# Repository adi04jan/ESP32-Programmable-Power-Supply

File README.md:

# Voltbench — ESP32-C3 Programmable Power Supply

A three-channel bench power supply controlled over Wi-Fi, built around an **ESP32-C3 Super Mini**. The variable channel uses an LM2596-ADJ buck converter set by an MCP4017 I2C digital potentiometer, driven by a calibration-map "deadbeat" controller: it jumps to the mapped wiper step, verifies with one filtered ADC sample, applies at most one single-step correction, and freezes — no hunting, settled in under a second. Two fixed rails deliver regulated 5 V and 3.3 V. Everything is managed through a dark-themed responsive web UI served directly from the microcontroller — no app, no cloud, no dependencies.

Designed and developed by **Aditya Biswas**.

---

## Screenshots

| Dashboard | History | Settings |
|-----------|---------|----------|
|  |  |  |

---

## Features

### Power Outputs
| Channel | Rail | Range | Regulation |
|---------|------|-------|------------|
| CH1 | LM2596-ADJ (variable) | 2.5 V – 15 V | map-based deadbeat control + on-device calibration sweep |
| CH2 | Mini360 (fixed 5 V) | 5.0 V | Passthrough (monitor only) |
| CH3 | LM1117-3.3 (LDO, fixed) | 3.3 V | Passthrough (monitor only) |

### Accuracy (measured, after calibration sweep)
| Setpoint | Measured | Error |
|----------|----------|-------|
| 3.3 V | 3.22 V | −80 mV (2.4%) |
| 5.0 V | 4.99 V | −10 mV (0.2%) |
| 9.0 V | 8.98 V | −20 mV (0.2%) |
| 12.0 V | 12.29 V | +290 mV (2.4%) |
| 15.0 V | 15.55 V | +550 mV (3.7%) |

> Accuracy is limited by wiper-step quantization (~27 mV/step at low voltages, up to ~1 V/step near the ceiling). Run Settings → Calibration → Run sweep once after assembly (CH1 unloaded).

### Web UI
- **Dashboard** — live voltage at 4 Hz, per-channel enable toggles, voltage slider, preset chips (right-click to delete, ＋ to save current), delta indicator, All Off button
- **History** — bezier-smoothed time-series graph with SMA noise reduction, channel filters, event markers (output on/off), adjustable time window (1 min – 12 h)
- **Settings** — mDNS hostname, security/login, Wi-Fi management (scan/connect/forget, stores up to 4 SSIDs), OTA update, experimental flags (dial mode, EMA smoothing, fast poll), MQTT bridge
- **Calibration card** — run/clear the CH1 calibration sweep and see whether a valid map is loaded
- **Device log pane** — live firmware log streamed over a view-only WebSocket (`/logws`)
- **Web-upload OTA** — flash a `.bin` straight from the browser, with real upload/flash progress

### Connectivity
- **WebSocket** `/ws` — server pushes full status JSON at up to 4 Hz; also accepts control commands
- **REST API** — full control and configuration via `/api/*` endpoints
- **mDNS** — reachable at `http://voltbench.local/` on any mDNS-capable host (Windows, macOS, Linux, iOS)
- **Captive portal** — automatically falls back to AP mode (`VoltbenchAP`) when no saved Wi-Fi connects; re-tries every 30 s
- **Telnet console** (`:23`) and USB serial console — single-letter commands: `v<volts>` set CH1, `o1`/`o0` output on/off, `m` run calibration sweep, `c` cal status, `?` full state dump

### Management
- **OTA update** — pulls firmware from this repo's GitHub "latest release" assets on demand or auto-check on boot; web-upload OTA as a second, USB-free path
- **NVS persistence** — all settings, the CH1 calibration map, and Wi-Fi credentials survive power cycles and OTA updates
- **MQTT bridge** — publishes 1 Hz telemetry; subscribes to control topics
- **Factory reset** — wipes all NVS from Settings → Factory Reset
- **Token auth** — optional bearer-token login (stored in `sessionStorage`, persists across reboots)

---

## Hardware

### Bill of Materials

| Component | Part | Notes |
|-----------|------|-------|
| MCU | ESP32-C3 Super Mini | 4 MB flash, Wi-Fi 802.11 b/g/n |
| Variable regulator | LM2596-ADJ module | Adjustable buck, ~3–35 V input |
| Fixed 5 V | Mini360 module | Fixed-output synchronous buck |
| Fixed 3.3 V | LM1117-3.3 | LDO, TO-92 or SOT-223 |
| Digital pot | MCP4017T-103E/LT | 10 KΩ, 128 steps, I2C @ 0x2F |
| R1 (feedback) | 10 KΩ 1% | VOUT → FB (ADJ) on LM2596 |
| R_adc_top | 47 KΩ | CH1 ADC voltage divider high-side |
| R_adc_bot | 1 KΩ | CH1 ADC voltage divider low-side |
| R_5v / R_3v3 | 10 KΩ × 4 | CH2 and CH3 ADC dividers (÷2 each) |
| Enable switches | N-ch MOSFET or relay × 3 | Logic-level control from GPIO 5/6/7 |

### Pin Map

| GPIO | Function |
|------|----------|
| 0 | ADC CH1 — variable rail (47K:1K divider, ×48 scale) |
| 1 | ADC CH2 — 5 V rail (10K:10K divider, ×2 scale) |
| 3 | ADC CH3 — 3.3 V rail (10K:10K divider, ×2 scale) |
| 5 | Enable CH1 (variable output) |
| 6 | Enable CH2 (5 V output) |
| 7 | Enable CH3 (3.3 V output) |
| 8 | I2C SDA → MCP4017 |
| 9 | I2C SCL → MCP4017 |

### LM2596-ADJ Feedback Network

```
VOUT ──── 10 KΩ ──── FB (ADJ) ──── MCP4017 wiper ──── GND
                                     (0 – 10 KΩ)
```

`Vout = 1.235 × (1 + 10 000 / R2)` where R2 is the MCP4017 resistance.

| Target | R2 needed | MCP4017 step |
|--------|-----------|--------------|
| 2.5 V | 9.87 KΩ | 125 / 127 |
| 5.0 V | 3.27 KΩ | 41 / 127 |
| 9.0 V | 1.56 KΩ | 20 / 127 |
| 12.0 V | 1.13 KΩ | 14 / 127 |
| 15.0 V | 0.87 KΩ | 11 / 127 |

### CH1 ADC Divider

```
VOUT ──── 47 KΩ ──── GPIO0 ──── 1 KΩ ──── GND
                       ↑
                  ADC reads here (0 – 2.5 V with ADC_11db)
                  Scale factor = 48 → supports up to ~27 V
```

---

## Firmware

### Prerequisites

- **Arduino IDE 2.x** with ESP32 Arduino core (Espressif) v3.x
- Libraries (Library Manager):
  - `ESPAsyncWebServer` + `AsyncTCP`
  - `ArduinoJson` v7
  - `PubSubClient` *(only if MQTT is needed)*

  (The MCP4017 digital pot is driven with direct I2C register writes — no digital-pot library needed.)

### Build & Flash

1. Clone the repository:
   ```sh
   git clone https://github.com/your-username/ESP32-Programmable-Power-Supply.git
   ```

2. Edit `ESP32_power_supply/credential.h` with your Wi-Fi credentials (these only seed NVS the first time — if any SSID slot is already saved, they're ignored):
   ```cpp
   static const char *ssids[]     = { "YourSSID" };
   static const char *passwords[] = { "YourPassword" };
   ```
   OTA is not configurable here — it's pinned to this repo's GitHub "latest release" assets (see [OTA Updates](#ota-updates)).

3. In Arduino IDE, set:
   - Board: `ESP32C3 Dev Module`
   - Upload Speed: `921600`
   - Flash Size: `4MB`
   - Partition Scheme: **Custom** → select `ESP32_power_supply/partitions.csv`

4. Upload: **Sketch → Upload** (`Ctrl+U`)

5. Open Serial Monitor at **115200 baud** — you should see:
   ```
   Voltbench v3.0.0 booting...
   MCP4017 OK @ 0x2F
   Joined YourSSID — IP=192.168.x.x
   URL: http://voltbench.local/
   ```

6. Open `http://voltbench.local/` in any browser on the same network.

### Partition Layout

```
nvs        20 KB   Settings and Wi-Fi credentials
otadata     8 KB   OTA slot tracking
app0     1792 KB   Active firmware (~1.3 MB used)
app1     1792 KB   OTA staging slot
spiffs    448 KB   Reserved
```

### Regenerating the Web UI

After editing `new design/Power Supply.html`, run this PowerShell snippet to rebuild `web_page.h`:

```powershell
$html  = Get-Content "new design\Power Supply.html" -Raw -Encoding utf8
$bytes = [System.Text.UTF8Encoding]::new($false).GetBytes($html)
$ms    = [System.IO.MemoryStream]::new()
$gz    = [System.IO.Compression.GzipStream]::new($ms, [System.IO.Compression.CompressionLevel]::Optimal)
$gz.Write($bytes, 0, $bytes.Length); $gz.Close()
$gzBytes = $ms.ToArray()
$chunks  = for ($i = 0; $i -lt $gzBytes.Length; $i += 16) {
    "  " + (($gzBytes[$i..([Math]::Min($i+15,$gzBytes.Length-1))] |
    ForEach-Object { "0x{0:x2}" -f $_ }) -join ", ")
}
$header = @("#pragma once","const uint8_t index_html_gz[] PROGMEM = {",
            ($chunks -join ",`n"),"};",
            "const size_t index_html_gz_len = $($gzBytes.Length);")
[System.IO.File]::WriteAllLines("ESP32_power_supply\web_page.h", $header,
    [System.Text.UTF8Encoding]::new($false))
Write-Host "Done: $($bytes.Length) -> $($gzBytes.Length) bytes"
```

---

## Usage

### Calibration

On first flash CH1 has no calibration map, so the deadbeat controller falls back to a coarse built-in estimate. For rated accuracy, run the sweep once:

1. **Disconnect any load from CH1** — the sweep drives the output across its full range (~2.5 V → ceiling) and needs the rail unloaded to read clean.
2. In **Settings → Calibration**, click **Run sweep**. It steps the MCP4017 through all 128 positions, sampling each one — takes about a minute. The busy state is reported as `"busy"` in `/api/status` and rejects a second sweep request while running.
3. The resulting step→millivolt map is smoothed to be monotonic, marked valid, and persisted to NVS — it survives reboots and OTA updates (NVS is a separate flash partition the OTA slot swap never touches).

Re-run the sweep only if the hardware changes (different MCP4017, feedback resistor, or LM2596 module). Use **Clear** to wipe the map and fall back to the coarse estimate.

### Presets

- **Click** a preset chip to jump to that voltage instantly.
- **Right-click** a chip to delete it.
- **＋** saves the current slider position as a new preset (stored in browser `localStorage`).

### All Off

The **All off** button in the top-right cuts all three outputs simultaneously. Individual toggles restore each channel independently.

---

## REST API

All responses are JSON. When `require_login` is enabled, include header `X-Auth: <token>` on every request except `/api/login`.

| Method | Path | Description |
|--------|------|-------------|
| `GET` | `/api/status` | Live voltages and controller state |
| `GET` | `/api/info` | Device info, network, settings |
| `POST` | `/api/login` | `pass=…` → `{ok, token}` |
| `POST` | `/api/control` | Outputs and voltage (see below) |
| `POST` | `/api/settings` | JSON — any subset of settings |
| `GET` | `/api/wifi/scan` | Start scan → returns networks |
| `POST` | `/api/wifi/connect` | `ssid=…&pass=…` |
| `POST` | `/api/wifi/forget` | `ssid=…` |
| `GET` | `/api/ota/check` | Check GitHub for newer firmware (async: `202 {"checking":true}` while in flight) |
| `POST` | `/api/ota/update` | Pull from GitHub if newer |
| `POST` | `/api/ota/force` | Pull from GitHub unconditionally |
| `POST` | `/api/ota/upload` | Multipart `.bin` upload → flashes the inactive OTA slot, reboots on success |
| `POST` | `/api/cal/sweep` | Start the CH1 calibration sweep (`409` if the controller is already busy) |
| `GET` | `/api/cal/status` | `{valid, running, mv:[128 values]}` |
| `POST` | `/api/cal/clear` | Wipe the calibration map |
| `GET` | `/api/mqtt/test` | Test broker connectivity |
| `POST` | `/api/reboot` | Restart device |
| `POST` | `/api/factory_reset` | Wipe NVS |

**`/api/control` actions** (form-encoded POST body):
```
action=toggle&output=1&value=1
action=set_voltage&output=1&value=5.0
action=all_off
```

**`/api/status` example:**
```json
{
  "output1": true,  "output2": false, "output3": false,
  "voltage1": 4.99, "voltage2": 5.17, "voltage3": 3.31,
  "set1": 5.0,
  "cal": true,
  "state": "frozen",
  "ts": 8040468
}
```

`state`: `idle` | `settling` | `verifying` | `frozen` | `busy` (`busy` = calibration sweep in progress). `voltage1` is the median-of-5 display value; `cal` reports whether a valid calibration map is loaded.

`/api/info` unauthenticated returns `{fw, mdns, require_login, captive}`; with a valid token it adds `ip, mac, ssid, rssi, uptime, ota:{auto}, exp:{fast,smooth,dial}, mqtt:{…}, saved_ssids, vmax`.

---

## WebSocket

Connect to `ws://voltbench.local/ws`.

The server **pushes** a full status frame automatically — every 250 ms with the fast-poll flag on, every 1 s otherwise — no subscription needed. `ws://voltbench.local/logws` is a second, view-only socket that streams the live firmware debug log (used by the Device log pane).

**Send a control command:**
```json
{ "action": "set_voltage", "output": 1, "value": 9.0 }
{ "action": "toggle",      "output": 1, "value": true }
{ "action": "all_off" }
```

When `require_login` is on, include `"token": "<token>"` in every command.

**Quick test (browser console):**
```js
const ws = new WebSocket('ws://voltbench.local/ws');
ws.onmessage = e => console.log(JSON.parse(e.data));
ws.onopen    = () => ws.send(JSON.stringify({action:'set_voltage', output:1, value:5.0}));
```

---

## MQTT

Enable in **Settings → MQTT**. Configure broker host, port, credentials, and topic prefix.

| Topic | Direction | Payload |
|-------|-----------|---------|
| `voltbench/tele` | Publish (1 Hz) | Full JSON telemetry (same shape as `/api/status`) |
| `voltbench/status` | Publish (retained, on connect) | `online` |
| `voltbench/cmd/ch1/output` | Subscribe | `on` / `off` / `1` / `0` |
| `voltbench/cmd/ch2/output` | Subscribe | `on` / `off` / `1` / `0` |
| `voltbench/cmd/ch3/output` | Subscribe | `on` / `off` / `1` / `0` |
| `voltbench/cmd/ch1/voltage` | Subscribe | Float string, e.g. `5.0` — clamped to `[0, 16]`, invalid channels/values are silently ignored |

The prefix `voltbench` is configurable in Settings → MQTT → Topic prefix. Only CH1 accepts a voltage command (CH2/CH3 are fixed rails); toggling CH2/CH3 output is still valid.

---

## OTA Updates

Two independent paths, no local server required:

1. **Pull-OTA from GitHub** — the base URL is pinned in firmware to this repo's `/releases/latest/download/` assets (HTTPS, **without** certificate verification — `WiFiClientSecure::setInsecure()` is used deliberately; there's no local CA store on this MCU, and this is an accepted trade-off, not an oversight). The device fetches `version.txt`, compares it to `CURRENT_FIRMWARE_VERSION`, and — on `/api/ota/update`, `/api/ota/force`, or the optional auto-check on boot — downloads `firmware_<version>.bin` into the inactive OTA slot and reboots on success. To ship a release: tag it, then attach `version.txt` and `firmware_<version>.bin` to the GitHub release; `/releases/latest/download/` resolves automatically.
2. **Web-upload OTA** — `POST` a compiled `.bin` to `/api/ota/upload` (multipart, e.g. `curl -H "X-Auth: <token>" -F "f=@ESP32_power_supply.ino.bin" http://voltbench.local/api/ota/upload`), or use the **Update** button in Settings for the same flow with a progress bar. No GitHub, no USB.

Either path rejects a second update while one is already running (logged as `busy`).

---

## Architecture

```
┌────────────────────────────────────────────────────┐
│  ESP32-C3  (FreeRTOS, single physical core)        │
│                                                    │
│  ┌──────────────────────┐  volatile globals         │
│  │  voltageControlTask  │◄────────────────────────┐ │
│  │  (priority 2, core 0)│  g_target_mV            │ │
│  │                      │  g_setpoint_mV          │ │
│  │  deadbeat state      │  g_measured_mV          │ │
│  │  machine: idle →     │  g_display_mV  ────────►│ │
│  │  settling → verify   │  g_5v_mV / g_3v3_mV     │ │
│  │  → frozen (or busy   │  g_vctrl_state          │ │
│  │  during cal sweep)   │  g_cal_mv[128] / valid  │ │
│  │  ADC reads (all 3    │                         │ │
│  │  rails) + I2C pot    │                         │ │
│  └──────────────────────┘                         │ │
│                                                   │ │
│  ┌──────────────────────┐                         │ │
│  │  AsyncWebServer      │─────────────────────────┘ │
│  │  ESPAsyncWebServer   │  Reads the globals above  │
│  │                      │  Writes g_target_mV       │
│  │  /api/* handlers     │                           │
│  │  WebSocket push      │                           │
│  └──────────────────────┘                           │
│                                                     │
│  loop():  vb_loop()                                 │
│     DNS captive · WS push · MQTT · OTA · console    │
└────────────────────────────────────────────────────┘
        │ I2C                │ ADC_11db
    MCP4017 @ 0x2F        GPIO 0 / 1 / 3
    10 KΩ, 128 steps      ×48 / ×2 / ×2
        │
   LM2596-ADJ
   feedback R2
```

**Key design decisions:**
- `voltageControlTask` owns ALL ADC sampling (all three rails) and the I2C pot; web handlers read atomically-written globals only. Status reads use `g_display_mV`, a median-of-5 window snapped on freeze for a calm steady-state number.
- The controller is a calibration-map deadbeat, not a feedback loop: predict the wiper step from `g_cal_mv[]`, wait 300 ms to settle, take one ~200 ms filtered verify sample, apply at most one ±1-step correction, then freeze (`g_vctrl_state`: idle → settling → verifying → frozen). No PID, no hunting, no per-cycle recomputation — settled in under a second across the full range. Without a calibration map it falls back to a coarse built-in R↔step estimate.
- The web UI is a single gzip-compressed HTML file (~23 KB) served directly from PROGMEM — no filesystem partition required.

---

## Troubleshooting

| Symptom | Cause | Fix |
|---------|-------|-----|
| `voltbench.local` not resolving | mDNS client issue | Try IP directly; Android needs an mDNS helper app |
| Voltage shows 0 V with output OFF | Expected — enable pin cuts power | Toggle output ON |
| CH1 settles far from setpoint | No calibration map — coarse fallback estimate in use | Run Settings → Calibration → Run sweep (CH1 unloaded) |
| OTA "check" never returns `newer` | No release published yet, or `version.txt`/`.bin` missing from the GitHub release | Confirm the tag's release has both assets attached |
| `MCP4017 not found!` at boot | I2C wiring | Check SDA/SCL and pull-up resistors (4.7 KΩ to 3.3 V) |
| Sketch too large to upload | Wrong partition scheme | Select Custom and point to `partitions.csv` |
| Settings revert after save | Browser cached old page | Hard-refresh (`Ctrl+Shift+R`) |

---

## License

MIT — see [LICENSE](LICENSE).

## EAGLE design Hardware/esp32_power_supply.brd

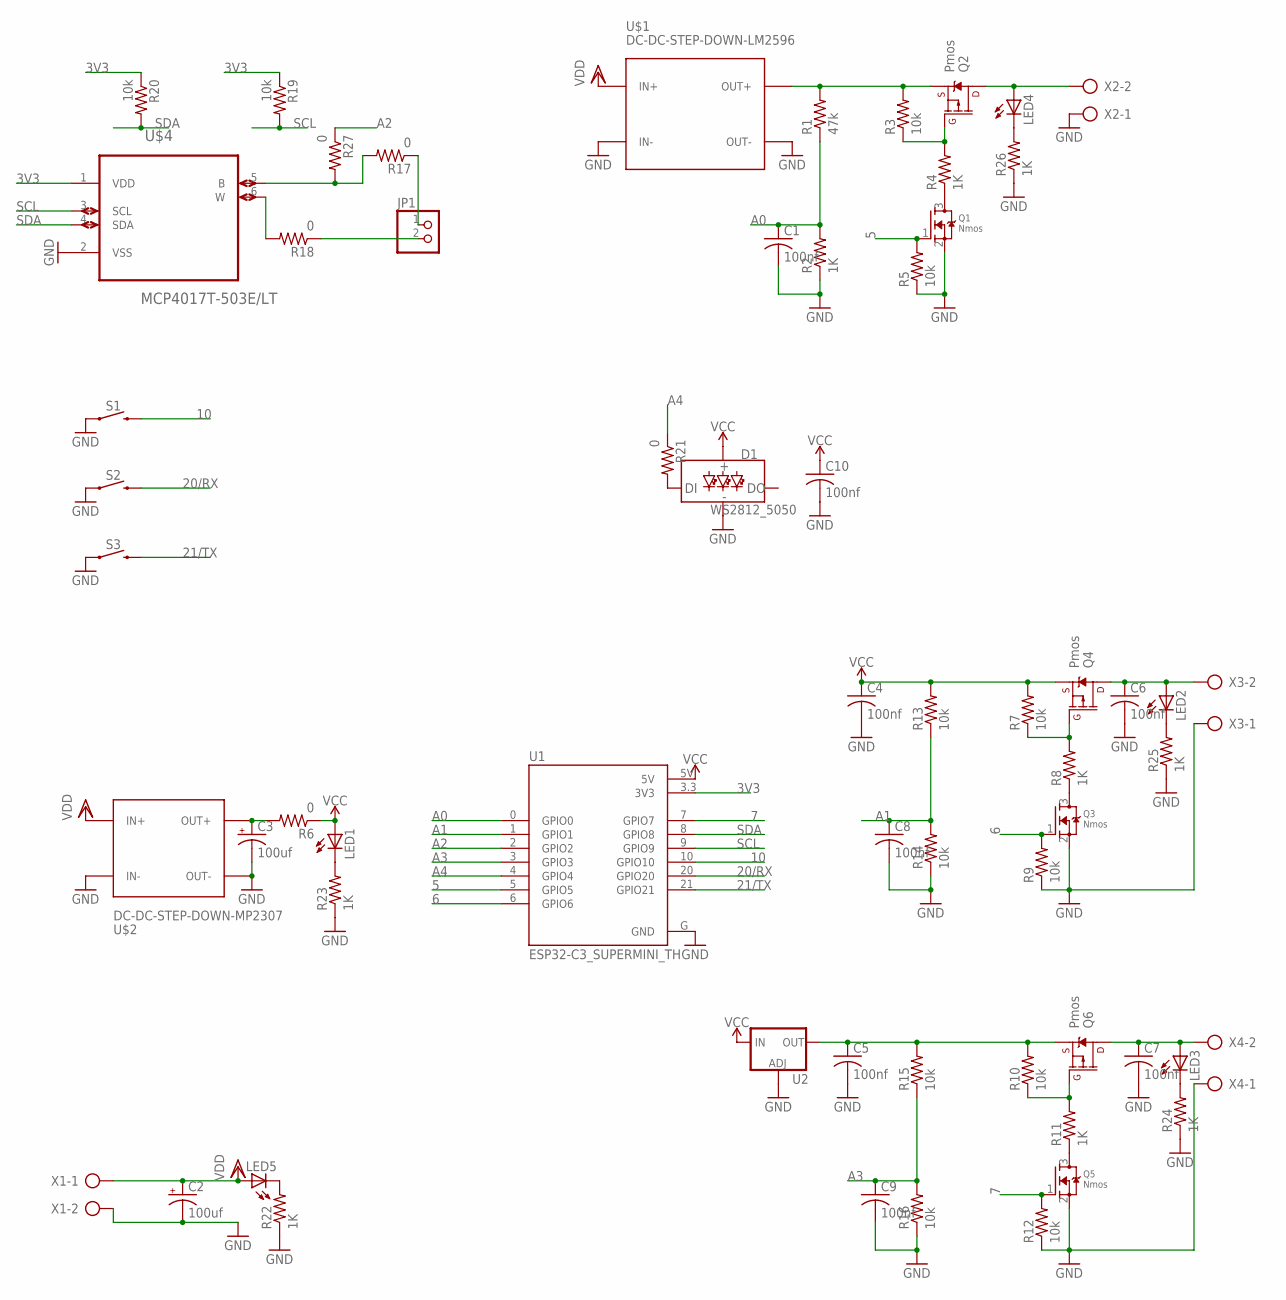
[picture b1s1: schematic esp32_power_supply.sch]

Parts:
C1, C4, C5, C6, C7, C8, C9, C10: 100nf; C1206K
C2, C3: 100uf; E3,5-10
D1: WS2812_5050; WS2812-5X5-4PIN
JP1: PINHD-1X2; 1X02
LED1, LED2, LED3, LED4, LED5: LEDSMT1206; 1206
Q1, Q3, Q5: Nmos; SOT23
Q2, Q4, Q6: Pmos; SOT23-3
R1: 47k; M1206
R2, R4, R8, R11, R22, R23, R24, R25, R26: 1K; M1206
R3, R5, R7, R9, R10, R12, R13, R14, R15, R16, R19, R20: 10k; M1206
R6, R17, R18, R21, R27: 0; M1206
S1, S2, S3: MOMENTARY-SWITCH-SPST-PTH-6.0MM; TACTILE_SWITCH_PTH_6.0MM
U1: ESP32-C3_SUPERMINI_TH; MODULE_ESP32-C3_SUPERMINI_TH
U2: V_REG_LM1117SOT223; SOT223
U$1: DC-DC-STEP-DOWN-LM2596
U$2: DC-DC-STEP-DOWN-MP2307
U$4: MCP4017T-503E/LT; SOT65P210X110-6N
X1, X2, X3, X4: AK500/2-H

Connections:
3V3: R19.1, R20.1, U1.3.3 (3V3), U$4.1 (VDD)
5: Q1.1 (G), R5.2, U1.5 (GPIO5)
6: Q3.1 (G), R9.2, U1.6 (GPIO6)
7: Q5.1 (G), R12.2, U1.7 (GPIO7)
10: S1.3 (2), U1.10 (GPIO10)
20/RX: S2.3 (2), U1.20 (GPIO20)
21/TX: S3.3 (2), U1.21 (GPIO21)
A0: C1.1, R1.1, R2.2, U1.0 (GPIO0)
A1: C8.1, R13.1, R14.2, U1.1 (GPIO1)
A2: R27.1, U1.2 (GPIO2)
A3: C9.1, R15.1, R16.2, U1.3 (GPIO3)
A4: R21.1, U1.4 (GPIO4)
GND: C1.2, C2.-, C3.-, C4.2, C5.2, C6.2, C7.2, C8.2, C9.2, C10.2, D1.GND, Q1.2 (S), Q3.2 (S), Q5.2 (S), R2.1, R5.1, R9.1, R12.1, R14.1, R16.1, R22.1, R23.1, R24.1, R25.1, R26.1, S1.1, S2.1, S3.1, U1.G (GND), U2.1 (ADJ), U$1.IN-, U$1.OUT-, U$2.IN-, U$2.OUT-, U$4.2 (VSS), X1.2, X2.1, X3.1, X4.1
unnamed: Q2.2 (S), R1.2, R3.2, U$1.OUT+
unnamed: D1.DI, R21.2
unnamed: Q2.1 (G), R3.1, R4.2
unnamed: LED4.A, Q2.3 (D), X2.2
unnamed: Q1.3 (D), R4.1
unnamed: LED5.C, R22.2
unnamed: C3.+, R6.2, U$2.OUT+
unnamed: LED1.C, R23.2
unnamed: Q4.1 (G), R7.1, R8.2
unnamed: C6.1, LED2.A, Q4.3 (D), X3.2
unnamed: Q3.3 (D), R8.1
unnamed: LED3.C, R24.2
unnamed: C5.1, Q6.2 (S), R10.2, R15.2, U2.2 (OUT), U2.4 (OUT)
unnamed: Q6.1 (G), R10.1, R11.2
unnamed: C7.1, LED3.A, Q6.3 (D), X4.2
unnamed: Q5.3 (D), R11.1
unnamed: LED2.C, R25.2
unnamed: LED4.C, R26.2
unnamed: R17.2, R27.2, U$4.5 (B)
unnamed: R18.2, U$4.6 (W)
unnamed: JP1.1, R17.1
unnamed: JP1.2, R18.1
SCL: R19.2, U1.9 (GPIO9), U$4.3 (SCL)
SDA: R20.2, U1.8 (GPIO8), U$4.4 (SDA)
VCC: C4.1, C10.1, D1.VCC, LED1.A, Q4.2 (S), R6.1, R7.2, R13.2, U1.5V, U2.3 (IN)
VDD: C2.+, LED5.A, U$1.IN+, U$2.IN+, X1.1

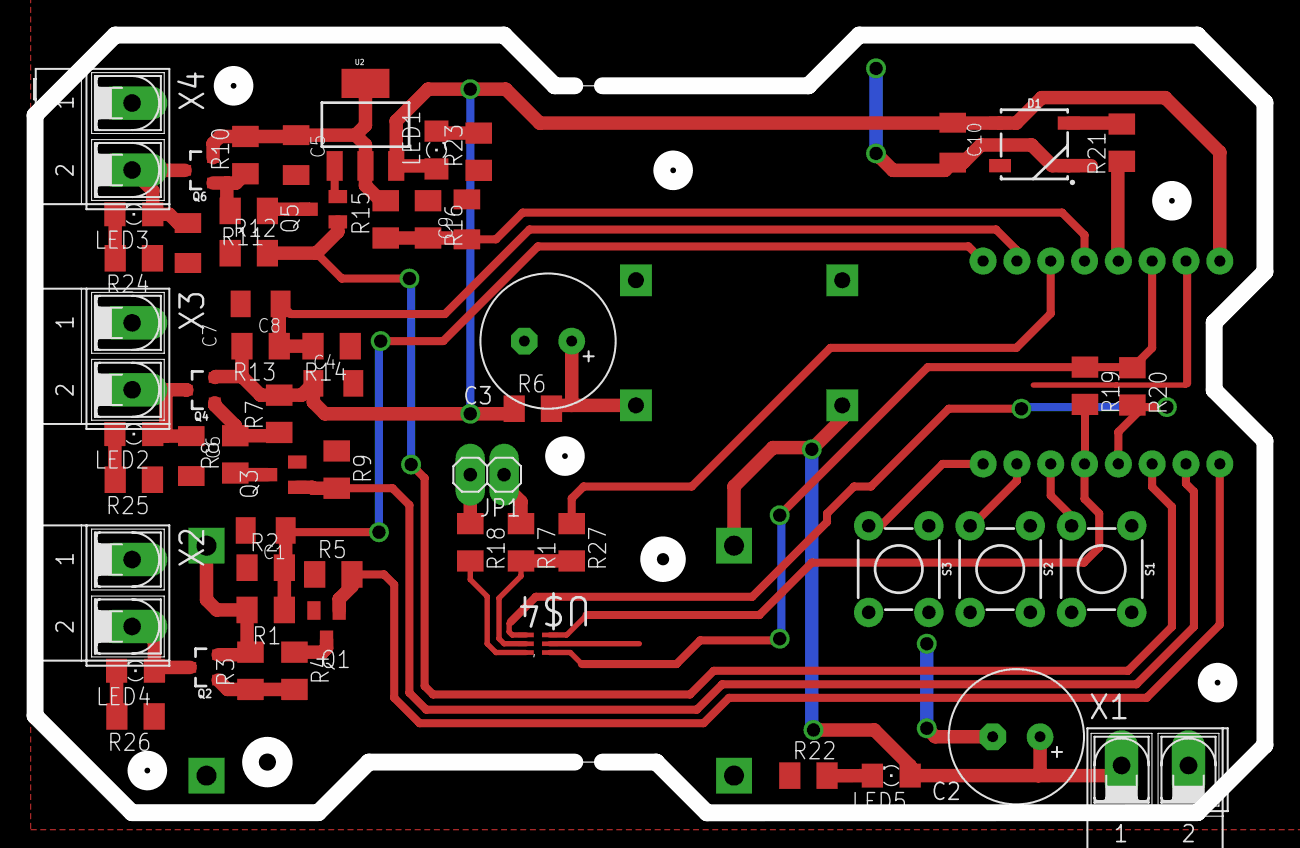
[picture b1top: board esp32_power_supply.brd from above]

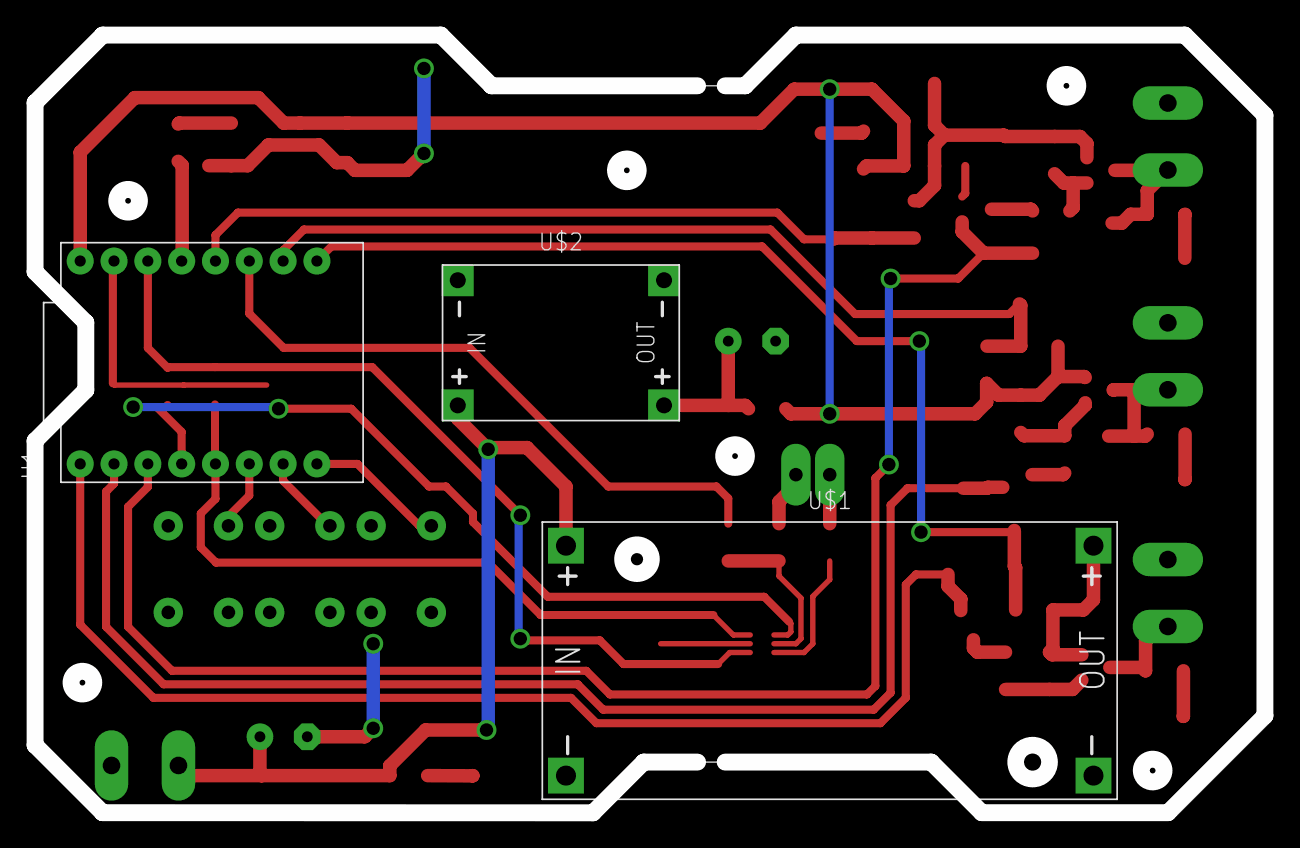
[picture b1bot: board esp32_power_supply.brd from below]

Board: 2 copper layers, 92.4 x 58.4 mm, 62 parts (3 on the bottom side), 39 nets.

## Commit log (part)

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2025-10-26 Added Readme
2025-10-26 Added Hardware files and board files
2025-10-26 Added software for the Power Supply
2025-10-28 Added live refresh and update in Webpage
2026-05-15 fix: correct inverted voltage tolerance check in set_voltage
2026-05-15 fix: reset WIFI_STATUS on disconnect so reconnect retries actually run
2026-05-15 fix: revert unauthorized version bump (keep at 0.0.1)
2026-05-15 fix: remove control_voltage global to eliminate async task race condition
2026-05-15 fix: no_network counter is now local so repeated calls retry properly
2026-05-15 fix: re-enable 5-sample moving average for VV ADC channel
2026-05-15 fix: use signed intermediate for resistance calc to prevent uint underflow
    - Replace uint64_t direct calculation with signed long intermediate
    - Add underflow protection: clamp to 0 if result is negative
    - Remove unused step_jump variable
2026-05-15 fix: replace expired DST Root CA X3 with ISRG Root X1, enforce HTTPS OTA URLs
2026-05-15 fix: add div-by-zero guard in set_voltage and unify tolerance comparison
    - Add early-return guard in set_voltage() to prevent division by zero when target_mV <= DC_V_REF (1235 mV)
    - Change tolerance comparison from < to <= in the set_voltage() loop to match fine_tune_volt() consistency
2026-05-15 feat: raise slider max to 19V and add 15V/19V quick-set buttons
2026-05-15 fix: rewrite voltage control to prevent runaway to max voltage
2026-05-15 feat: non-blocking FreeRTOS voltage control with measured voltage in status
    - Add four volatile globals (g_target_mV, g_setpoint_mV, g_measured_mV,
    g_ctrl_output1) for lock-free task communication
    - Add voltageControlTask (core 0, priority 2): formula-based set followed
    by fine-tune only when R2 > 3000 Ω (Vout ≤ ~5 V); fine-tune aborts if
    a new target arrives or voltage region is too coarse
    - Remove blocking fine_tune_volt(), set_voltage(), read_vv_fresh(),
2026-05-15 feat: browser shows measured + setpoint voltage, 1 s poll, slider drag guard
    - Add "Set: X.XV" label (setpoint1 span) below Output 1 measured display
    - Reduce /status poll from 2000 ms to 1000 ms
    - Guard measured display update with sliderDragging flag to prevent
    flicker while user is dragging the slider
    - Debounce setPresetVoltage buttons at 300 ms (same as slider)
2026-05-15 feat: Voltbench UI — full redesign with Dashboard/History/Settings tabs
    Web UI (Power Supply.html → gzip web_page.h, 82KB→22KB):
    - "Voltbench" dark theme with design tokens, Inter + JetBrains Mono fonts
    - 3-tab navigation: Dashboard (live outputs), History (canvas graph +
    event log), Settings (device, WiFi, security, OTA, guards, MQTT)
    - WebSocket live push at 4 Hz (falls back to polling)
    - Login/auth with bearer token (X-Auth header), stored in sessionStorage
2026-05-15 fix: resolve VBSettings forward-decl conflict and BOM in web_page.h
    Move ota_task_fn/perform_ota_tasked after #include firmware-additions.h
    so VBSettings vb is already in global scope; drop the conflicting local
    extern. Regenerate web_page.h without UTF-8 BOM.
2026-05-15 fix: replace HttpsOTAUpdate with built-in HTTPUpdate to reduce flash usage
    HttpsOTAUpdate bundles its own TLS/OTA stack (~100-150 KB extra).
    Switch to ESP32 core HTTPUpdate + WiFiClientSecure (shared mbedTLS,
    no added size). Drops the 3 KB ISRG cert string and HttpEvent stub.
    verify_ssl=true uses setInsecure() (encrypts but skips chain validation).
2026-05-15 feat: add custom 4MB partition table (1.75MB app, OTA-capable)
    Default and 'minimal' schemes only give 1.25-1.3MB to the app partition.
    Sketch is 1.34MB, so it overflows. Custom table gives 1.75MB per app
    partition while keeping OTA support (app0 + app1) and 448KB SPIFFS.
    Arduino IDE auto-detects partitions.csv in the sketch folder.
2026-05-15 feat: fix WiFi scan, voltage display, add WS commands + help page; optimize size
    Firmware:
    - captive AP now uses WIFI_AP_STA so scanNetworks() works in AP mode
    - vb_fill_status uses read_VV_volt() (5-sample smooth) not raw g_measured_mV
    - vb_on_ws_event processes incoming JSON commands (toggle/set_voltage/
    set_ilimit/all_off/clear_trip) with auth-token check; replies with status
    - Add #pragma GCC optimize("Os") to sketch (~50-80 KB savings)
2026-05-15 fix: ADC attenuation, security revert, fine-tune accuracy
    - Add analogSetAttenuation(ADC_11db) — fixes voltage display always
    showing <4 V by extending ADC range to 2500 mV (covers up to ~27.5 V
    on the ×11 divider) and eliminating saturation above ~10.4 V
    - Switch vb_fill_status() to g_measured_mV — eliminates concurrent ADC
    access between voltageControlTask and the AsyncWebServer task
    - Increase voltageControlTask FINE_TUNE_MAX from 3 to 8 iterations for
2026-05-15 fix: correct ADC multiplier ×48 (was ×11) and history timestamps
    - CH1 voltage divider is 47K:1K (×48 scale), not 10K:1K (×11).
    All four ADC read sites in .ino updated; fixes displayed voltage
    reading ~1/4 of actual output.
    - History CSV timestamps now use Date.now() (wall-clock) instead of
    s.ts (device uptime ms since boot), eliminating 1970-01-01 dates.
    - Regenerated web_page.h from updated HTML source.
2026-05-15 revert: restore ADC multiplier to ×11 (10K:1K divider)
    Previous commit wrongly changed to ×48 based on schematic showing R1=47K,
    but physical hardware has 10K and the original firmware was working correctly.
    The setup() comment "supports output up to ~27.5V" confirms ×11 (2500mV×11).
2026-05-15 fix: remove fine-tune loop, freeze pot on formula set, restore x48
    - Pot is now written once (formula) on target change then left alone.
    No iterative wiper adjustments that cause hunting at low voltages.
    - ADC averaging increased from 3 to 8 samples in both the post-set
    read and the idle monitor to reduce display noise at ~1V.
    - Restores x48 multiplier (confirmed correct by hardware measurement).
2026-05-15 feat: PID voltage controller with relay auto-tune
    - voltageControlTask is now a state machine: formula set → settling
    (300ms) → PID correction loop → converged (frozen). Pot only moves
    when actively correcting; freezes as soon as error < 100mV × 3 reads.
    - PID is linearised: output is voltage correction (mV), converted to
    ΔR using local dV/dR = −Vref×Rtop/R² so gains stay consistent
    across the full voltage range without hand-tuning per setpoint.
2026-05-15 fix: cast volatile uint8_t for min() template deduction
2026-05-15 fix: remove float-printf from PID/autotune to recover ~2-3KB flash
    Float format specifiers (%.0f, %.3f etc.) in Serial.printf pull in the
    full float-printf library. Replaced with integer x1000 output or removed
    debug prints entirely. Also dropped the redundant /api/pid GET endpoint
    (info already available via /api/info).
2026-05-15 perf: PID convergence under 1s via faster timing
    - ADC: 8x10ms=80ms -> 4x5ms=20ms (LM2596 settled well within 5ms)
    - Settle wait: 300ms -> 100ms
    - PID loop delay: 200ms -> 50ms when active, 200ms when monitoring
    - Convergence count: 3 -> 2 reads
    - Fast-path: if formula lands within 100mV on first read, converge
    immediately without running PID iterations at all
2026-05-16 docs: add comprehensive README with live screenshots
    Covers hardware BOM, pin map, feedback network, firmware build
    instructions, REST API, WebSocket, MQTT, OTA, architecture diagram,
    accuracy table (measured on hardware), and troubleshooting.
    Screenshots captured from live device at 192.168.1.21 (voltbench.local)
    during a full feature verification run.
2026-05-16 ui: display voltages as x.x V (1 decimal place)
2026-05-16 feat: add control modes + no-overvoltage voltage control
    Voltage control modes (quick/continuous/timed):
    - Quick: freezes wiper on 2 consecutive readings <150mV error, caches R per target
    - Continuous: keeps PID active until <100mV for 2 consecutive readings
    - Timed: PID runs for configurable timeout, freezes at best-seen R
    - g_ctrl_mode / g_ctrl_timeout_ms globals; persisted via NVS; exposed in /api/info
    and /api/settings; ctrl_mode reported in /api/status
2026-05-16 feat(ui): control mode selector, settings guard, fix api() Content-Type
    Control mode UI:
    - Control mode select (Quick / Continuous / Timed) added to PID card
    - Timed timeout dropdown (1/3/5/10s) shown only when Timed is selected
    - Save button now posts {pid:{kp,ki,kd}, ctrl:{mode,timeout_ms}} together
    - loadInfo() syncs ctrl.mode and ctrl.timeout_ms from /api/info response
    Settings form guard:
2026-05-17 chore: add .gitignore, untrack credential.h
    Ignore build artifacts, OTA test server, screenshots, and tool
    internals. Untrack credential.h so real WiFi credentials are never
    accidentally committed.
2026-05-17 chore: ignore new design draft files
2026-05-17 docs: add v2 hardware design document
    Full hardware design for two-channel bench PSU:
    MP1584 buck + PMOS LDO (FQP27P06 + LM358) + MCP4728 quad DAC +
    INA219 current/voltage sensing. Includes schematics, BOM,
    thermal analysis, PCB notes, and firmware interface.
2026-05-18 fix: always refresh credential.h SSIDs in NVS on every boot
    Remove the first-boot-only guard so hardcoded credentials from
    credential.h are written to NVS slots on every reset via
    vb_remember_wifi() (which deduplicates). Ensures the device
    picks up updated credentials without requiring a factory reset.
2026-05-18 fix: rewrite WiFi manager as FreeRTOS task; fix WiFi scan blocking
    Root cause: esp_wifi_connect() called during an active scan silently
    kills the scan with no WIFI_EVENT_SCAN_DONE event, leaving
    waitStatusBits() blocked for 60 s (the scan task timeout). This
    was triggered by vb_loop() calling vb_try_saved_wifi() immediately
    on the first loop iteration (lastRetry=0, millis()>30000 after
    the initial connection attempts).
2026-06-15 feat: stable voltage control, calibration map, live UI, WiFi flash + remote debug
    Output-1 control:
    - Replace the PID (which chased ADC noise and dithered the output between
    steps) with a deterministic best-step + freeze controller. Direct-I2C wiper
    writes bypass SW_MCP4017::setSteps()'s 4x-per-call Serial spam.
    - Heavily filter ADC feedback (50 samples / ~200 ms = ~10 mains cycles) to
    reject hum on the high-Z 47K:1K divider node.
2026-06-16 chore: bump firmware version to 2.0.0 for v2.0.0 release
2026-06-16 feat: pull-OTA from GitHub latest-release assets (HTTPS + redirect-follow)
    - perform_ota uses WiFiClientSecure (setInsecure) + HTTPC_FORCE_FOLLOW_REDIRECTS
    so it can fetch version.txt and firmware_<ver>.bin from GitHub releases.
    - OTA source set to /releases/latest/download/ so new releases auto-discover.
    - Auto-check moved off the boot path into a 16 KB task (TLS-safe) after the
    server starts; /api/ota/force now actually forces a re-flash.
2026-06-16 chore: bump firmware version to 2.0.1 (GitHub pull-OTA release)
2026-06-16 refactor: remove dead code
    - Drop unused SW_MCP4017 dependency + i2cDP object (wiper driven by direct I2C).
    - Remove unused read_VV_volt() and its extern.
    - Remove disabled ArduinoOTA (begin() hangs alongside AsyncTCP; web-upload OTA
    is the working WiFi-flash path) — include, begin helper, commented loop calls.
    - Remove write-only g_ctrl_output1.
    Also removed the _ota/ build-artifact dir (git-ignored).
2026-06-16 chore: remove superseded files (pot_diag characterization sketch, local ota_test_server)

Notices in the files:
parts and their libraries:
SparkFun-LED: Licensing: Creative Commons ShareAlike 4.0 International - https://creativecommons.org/licenses/by-sa/4.0
diy-modules: Released under the Creative Commons Attribution 4.0 International License: http://creativecommons.org/licenses/by/4.0
